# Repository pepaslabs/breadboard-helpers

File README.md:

# breadboard-helpers
A few breakout boards of commonly needed circuits when creating breadboard prototypes.

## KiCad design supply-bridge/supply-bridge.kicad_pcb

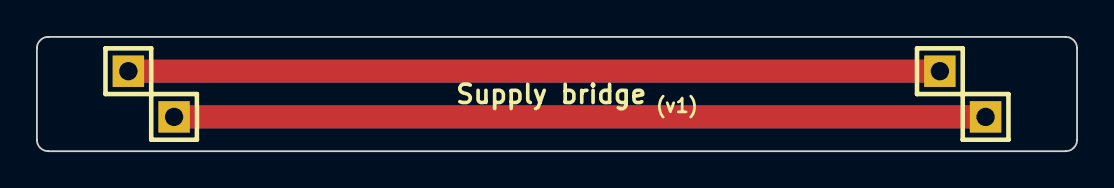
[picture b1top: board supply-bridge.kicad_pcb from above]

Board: 2 copper layers, 57.8 x 6.3 mm, 4 parts (0 on the bottom side), 2 nets.

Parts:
P1, P2, P3, P4: CONN_1X1; SIL-1

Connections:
GND: P2.1, P4.1
unnamed: P1.1, P3.1

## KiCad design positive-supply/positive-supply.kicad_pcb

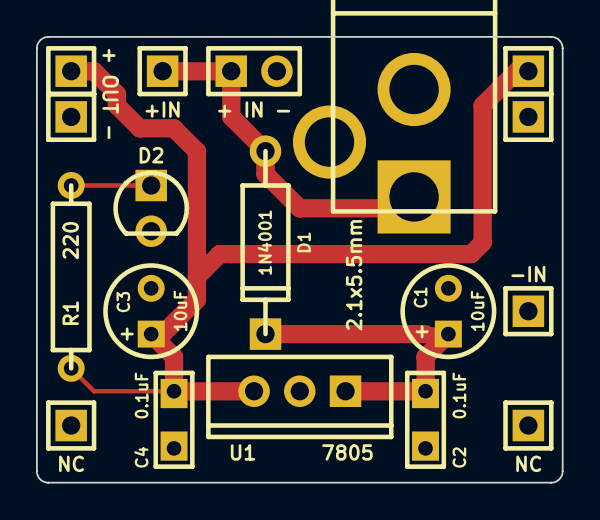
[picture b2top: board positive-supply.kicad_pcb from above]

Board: 2 copper layers, 29.2 x 24.8 mm, 18 parts (0 on the bottom side), 5 nets.

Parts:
C1, C3: 10uF; ELCAP_10_20_V_059A
C2, C4: 0.1uF; CERCAP_15_059B_0805
CON1: BARREL_JACK; BARREL_JACK_21x55
D1: 1N4001; DIODE_1A_069A_PL
D2: LED; LED_3MM_069A
P1: CONN_2X1; SIL-2
P2, P3, P4, P5, P6, P7, P8, P9: CONN_1X1; SIL-1
R1: 220; R_AXIAL_0W25_059A_PL
U1: 7805; TO-220_V_069A

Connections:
GND: C1.2, C2.2, C3.2, C4.2, CON1.2, D2.2, P1.2, P3.1, P5.1, P9.1, U1.2
unnamed: D2.1, R1.2
unnamed: C3.1, C4.1, P4.1, P8.1, R1.1, U1.3
unnamed: CON1.1, D1.1, P1.1, P2.1
unnamed: C1.1, C2.1, D1.2, U1.1

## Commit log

2017-07-09 Initial release
2017-07-09 minimum OSHPark board width is 0.25 inches
2017-07-09 adding board renders
